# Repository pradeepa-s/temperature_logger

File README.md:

# Temperature Logger

A temperature logger project to start learning fundamentals of product design.

# Tests

## Behavioral

Behavioural tests are implemented for the design and they can be found in tests/behavior folder.

### Setup

1. Install Python 3.6 or above
1. Install behave
1. Install ST-LINK-CLI (comes with STLink utility)
1. Ensure that the ST-LINK-CLI is in the path

### How to run tests?

Run all the tests:

```
behave
```

Run a test with tag @test_tag:

```
behave -t @test_tag
```

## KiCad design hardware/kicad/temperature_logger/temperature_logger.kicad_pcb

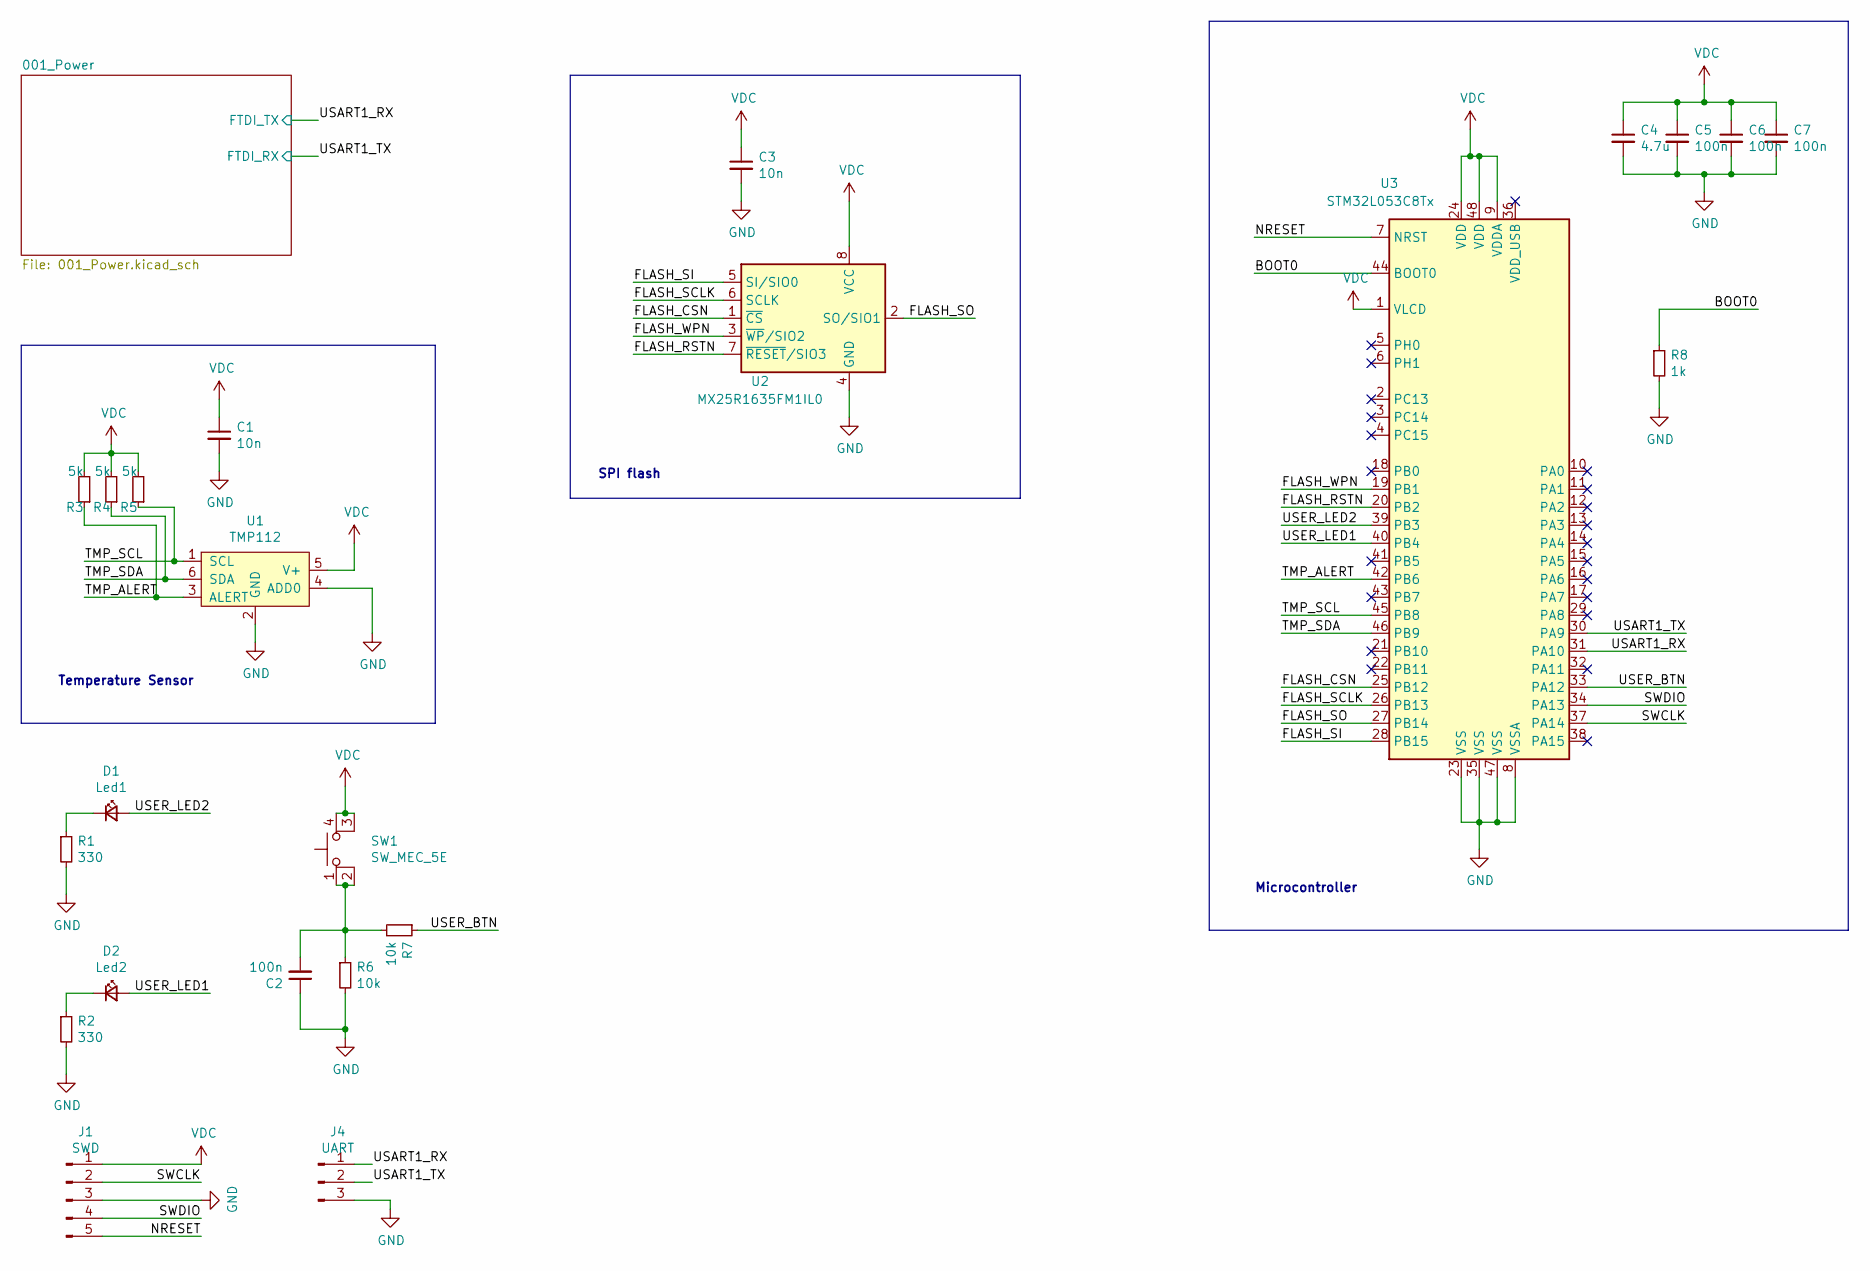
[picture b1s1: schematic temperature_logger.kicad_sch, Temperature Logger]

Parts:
C1, C3: 10n; C_0603_1608Metric_Pad1.08x0.95mm_HandSolder
C2, C5, C6, C7: 100n; C_0603_1608Metric_Pad1.08x0.95mm_HandSolder
C4: 4.7u; C_0603_1608Metric_Pad1.08x0.95mm_HandSolder
D1: Led1; LED_0603_1608Metric_Pad1.05x0.95mm_HandSolder
D2: Led2; LED_0603_1608Metric_Pad1.05x0.95mm_HandSolder
J1: SWD; PinHeader_1x05_P2.54mm_Vertical
J4: UART; PinHeader_1x03_P2.54mm_Vertical
R1, R2: 330; R_0603_1608Metric_Pad1.05x0.95mm_HandSolder
R3, R4, R5: 5k; R_0603_1608Metric_Pad1.05x0.95mm_HandSolder
R6, R7: 10k; R_0603_1608Metric_Pad1.05x0.95mm_HandSolder
R8: 1k; R_0603_1608Metric_Pad1.05x0.95mm_HandSolder
SW1: SW_MEC_5E; SW_SPST_Omron_B3FS-101xP
U1: TMP112; SOT-666
U2: MX25R1635FM1IL0; SOP-8_3.9x4.9mm_P1.27mm
U3: STM32L053C8Tx; LQFP-48_7x7mm_P0.5mm

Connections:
/BOOT0: R8.1, U3.44 (BOOT0)
/FLASH_CSN: U2.1 (~CS), U3.25 (PB12)
/FLASH_RSTN: U2.7 (~RESET/SIO3), U3.20 (PB2)
/FLASH_SCLK: U2.6 (SCLK), U3.26 (PB13)
/FLASH_SI: U2.5 (SI/SIO0), U3.28 (PB15)
/FLASH_SO: U2.2 (SO/SIO1), U3.27 (PB14)
/FLASH_WPN: U2.3 (~WP/SIO2), U3.19 (PB1)
/NRESET: J1.5, U3.7 (NRST)
/SWCLK: J1.2, U3.37 (PA14)
/SWDIO: J1.4, U3.34 (PA13)
/TMP_ALERT: R3.1, U1.3 (ALERT), U3.42 (PB6)
/TMP_SCL: R5.1, U1.1 (SCL), U3.45 (PB8)
/TMP_SDA: R4.1, U1.6 (SDA), U3.46 (PB9)
/USART1_RX: J4.1, U3.31 (PA10); also elsewhere on the board
/USART1_TX: J4.2, U3.30 (PA9); also elsewhere on the board
/USER_BTN: R7.1, U3.33 (PA12)
/USER_LED1: D2.2 (A), U3.40 (PB4)
/USER_LED2: D1.2 (A), U3.39 (PB3)
GND: C1.2, C2.1, C3.2, C4.2, C5.2, C6.2, C7.2, J1.3, J4.3, R1.2, R2.2, R6.2, R8.2, U1.2 (GND), U1.4 (ADD0), U2.4 (GND), U3.8 (VSSA), U3.23 (VSS), U3.35 (VSS), U3.47 (VSS); also elsewhere on the board
unnamed: C2.2, R6.1, R7.2, SW1.1, SW1.2
unnamed: D1.1 (K), R1.1
unnamed: D2.1 (K), R2.1
VDC: C1.1, C3.1, C4.1, C5.1, C6.1, C7.1, J1.1, R3.2, R4.2, R5.2, SW1.3 (K), SW1.4 (A), U1.5 (V+), U2.8 (VCC), U3.1 (VLCD), U3.9 (VDDA), U3.24 (VDD), U3.48 (VDD); also elsewhere on the board

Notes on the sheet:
Microcontroller
SPI flash
Temperature Sensor

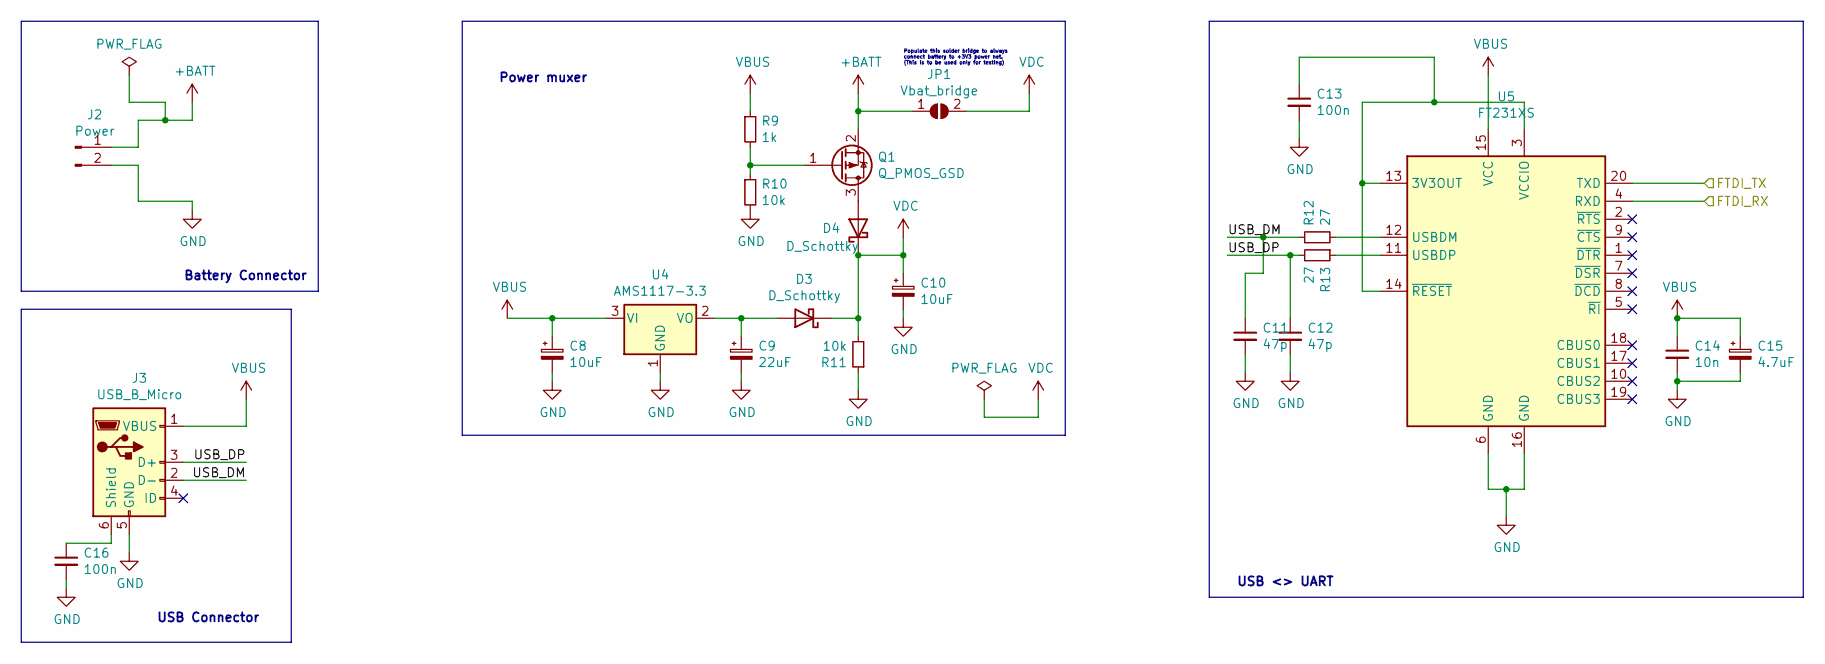
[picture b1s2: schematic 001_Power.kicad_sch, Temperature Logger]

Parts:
C8, C10: 10uF; CP_Elec_4x5.7
C9: 22uF; CP_Elec_4x5.7
C11, C12: 47p; C_0603_1608Metric_Pad1.08x0.95mm_HandSolder
C13, C16: 100n; C_0603_1608Metric_Pad1.08x0.95mm_HandSolder
C14: 10n; C_0603_1608Metric_Pad1.08x0.95mm_HandSolder
C15: 4.7uF; CP_Elec_4x5.7
D3, D4: D_Schottky; D_SOD-323_HandSoldering
J2: Power; BatteryHolder_Keystone_1060_1x2032
J3: USB_B_Micro; USB_Micro-B_Molex-105017-0001
JP1: Vbat_bridge; R_0603_1608Metric
Q1: Q_PMOS_GSD; SOT-23
R9: 1k; R_0603_1608Metric_Pad1.05x0.95mm_HandSolder
R10, R11: 10k; R_0603_1608Metric_Pad1.05x0.95mm_HandSolder
R12, R13: 27; R_0603_1608Metric_Pad1.05x0.95mm_HandSolder
U4: AMS1117-3.3; SOT-223-3_TabPin2
U5: FT231XS; SSOP-20_3.9x8.7mm_P0.635mm

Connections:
+BATT: J2.1, JP1.1 (A), Q1.2 (S)
/001_Power/USB_DM: C11.1, J3.2 (D-), R12.1
/001_Power/USB_DP: C12.1, J3.3 (D+), R13.2
/USART1_RX: U5.20 (TXD); also elsewhere on the board
/USART1_TX: U5.4 (RXD); also elsewhere on the board
GND: C8.2, C9.2, C10.2, C11.2, C12.2, C13.2, C14.2, C15.2, C16.2, J2.2, J3.5 (GND), R10.2, R11.1, U4.1 (GND), U5.6 (GND), U5.16 (GND); also elsewhere on the board
unnamed: C13.1, U5.3 (VCCIO), U5.13 (3V3OUT), U5.14 (~RESET)
unnamed: C16.1, J3.6 (Shield)
unnamed: C9.1, D3.2 (A), U4.2 (VO)
unnamed: D4.2 (A), Q1.3 (D)
unnamed: Q1.1 (G), R9.2, R10.1
unnamed: R12.2, U5.12 (USBDM)
unnamed: R13.1, U5.11 (USBDP)
VBUS: C8.1, C14.1, C15.1, J3.1 (VBUS), R9.1, U4.3 (VI), U5.15 (VCC)
VDC: C10.1, D3.1 (K), D4.1 (K), JP1.2 (B), R11.2; also elsewhere on the board

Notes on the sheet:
Battery Connector
USB Connector
Populate this solder bridge to always connect battery to +3V3 power net. (This is to be used only for testing)
Power muxer
USB <> UART

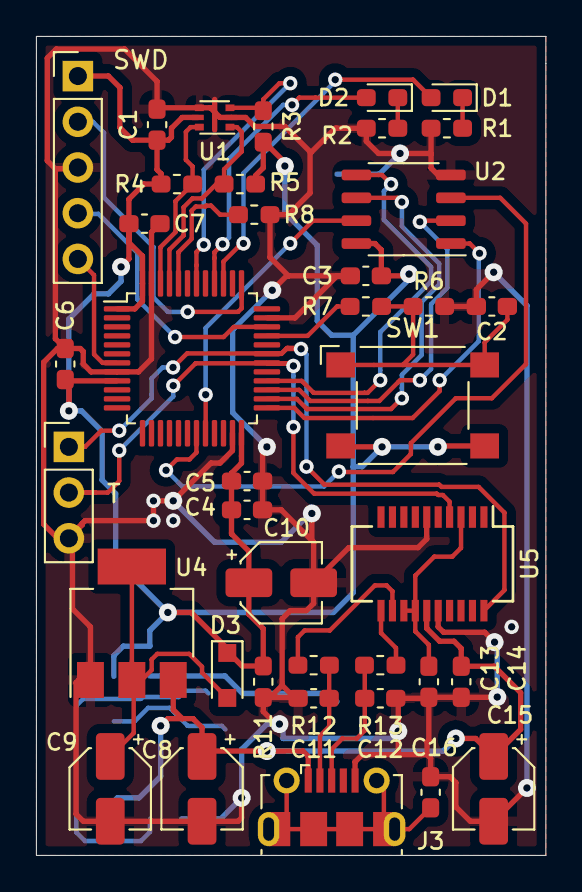
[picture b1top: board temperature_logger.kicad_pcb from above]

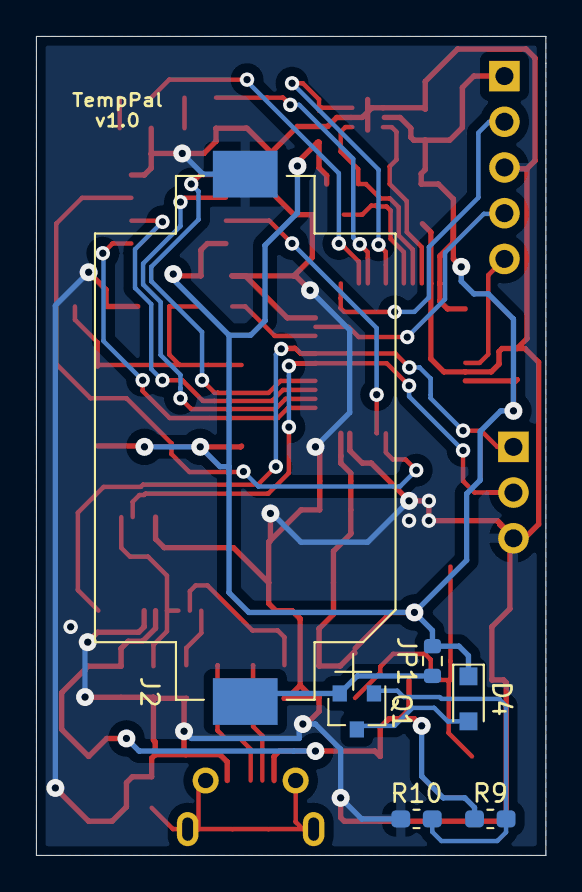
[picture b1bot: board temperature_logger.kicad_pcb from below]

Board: 2 copper layers, 28.3 x 45.5 mm, 45 parts (6 on the bottom side), 34 nets.

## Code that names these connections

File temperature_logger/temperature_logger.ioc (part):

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Mcu.Name=STM32L053C(6-8)Tx
Mcu.Package=LQFP48
Mcu.UserName=STM32L053C8Tx
PA0.GPIOParameters=GPIO_PuPd,GPIO_Label,GPIO_ModeDefaultEXTI
PA0.GPIO_Label=B1 [Blue PushButton]
PA0.GPIO_ModeDefaultEXTI=GPIO_MODE_EVT_RISING
PA0.GPIO_PuPd=GPIO_NOPULL
PA0.Signal=GPXTI0
PA1.GPIOParameters=GPIO_Label
PA1.GPIO_Label=MFX_WAKEUP
PA1.Signal=GPIO_Input
PA10.GPIOParameters=GPIO_Label
PA10.GPIO_Label=USART_RX
PA10.Mode=Asynchronous
PA10.Signal=USART1_RX
PA11.GPIOParameters=GPIO_Label
PA11.GPIO_Label=USB1_DM
PA11.Signal=USB_DM
PA12.GPIOParameters=GPIO_Label
PA12.GPIO_Label=USB1_DP
PA12.Signal=USB_DP
PA13.GPIOParameters=GPIO_Label
PA13.GPIO_Label=SWDIO
PA13.Signal=SYS_SWDIO
PA15.GPIOParameters=GPIO_Speed,GPIO_PuPd,GPIO_Label,GPIO_Mode
PA15.GPIO_Label=ePD1_CS [ePaper_CS\#]
PA15.GPIO_Mode=GPIO_MODE_AF_PP
PA15.GPIO_PuPd=GPIO_NOPULL
PA15.GPIO_Speed=GPIO_SPEED_FREQ_LOW
PA15.Signal=SPI1_NSS
PA2.Signal=TSC_G1_IO3
PA3.Signal=TSC_G1_IO4
PA5.GPIOParameters=GPIO_Speed,GPIO_PuPd,GPIO_Label,GPIO_ModeDefaultOutputPP
PA5.GPIO_Label=LD_R [LD4 Red Led]
PA5.GPIO_ModeDefaultOutputPP=GPIO_MODE_OUTPUT_PP
PA5.GPIO_PuPd=GPIO_NOPULL
PA5.GPIO_Speed=GPIO_SPEED_FREQ_LOW
PA5.Signal=GPIO_Output
PA6.Signal=TSC_G2_IO3
PA7.Signal=TSC_G2_IO4
PA8.GPIOParameters=GPIO_PuPd,GPIO_Label,GPIO_Mode
PA8.GPIO_Label=ePD1_BUSY [ePaper_BUSY]
PA8.GPIO_Mode=GPIO_MODE_INPUT
PA8.GPIO_PuPd=GPIO_NOPULL
PA8.Signal=GPIO_Input
PA9.GPIOParameters=GPIO_Label
PA9.GPIO_Label=USART_TX
PA9.Mode=Asynchronous
PA9.Signal=USART1_TX
PB0.Signal=TSC_G3_IO2
PB1.Signal=TSC_G3_IO3
PB10.GPIOParameters=GPIO_Speed,GPIO_PuPd,GPIO_Label,GPIO_ModeDefaultOutputPP
PB10.GPIO_Label=ePD1_PWR_ENn [ePaper_PowerOn]
PB10.GPIO_ModeDefaultOutputPP=GPIO_MODE_OUTPUT_PP
PB10.GPIO_PuPd=GPIO_NOPULL
PB10.GPIO_Speed=GPIO_SPEED_FREQ_LOW
PB10.Signal=GPIO_Output
PB11.GPIOParameters=GPIO_Speed,GPIO_PuPd,GPIO_Label,GPIO_ModeDefaultOutputPP
PB11.GPIO_Label=ePD1_D/C [ePaper_D/C\#]
PB11.GPIO_ModeDefaultOutputPP=GPIO_MODE_OUTPUT_PP
PB11.GPIO_PuPd=GPIO_NOPULL
PB11.GPIO_Speed=GPIO_SPEED_FREQ_LOW
PB11.Signal=GPIO_Output
PB12.GPIOParameters=GPIO_Label
PB12.GPIO_Label=NFC_NSS
PB12.Signal=SPI2_NSS
PB13.GPIOParameters=GPIO_Label
PB13.GPIO_Label=NFC_SCK
PB13.Signal=SPI2_SCK
PB14.GPIOParameters=GPIO_Label
PB14.GPIO_Label=NFC_MISO
PB14.Signal=SPI2_MISO
PB15.GPIOParameters=GPIO_Label
PB15.GPIO_Label=NFC_MOSI
PB15.Signal=SPI2_MOSI
PB2.GPIOParameters=GPIO_Speed,GPIO_PuPd,GPIO_Label,GPIO_ModeDefaultOutputPP
PB2.GPIO_Label=ePD1_RESET [ePaper_RES\#]
PB2.GPIO_ModeDefaultOutputPP=GPIO_MODE_OUTPUT_PP
PB2.GPIO_PuPd=GPIO_NOPULL
PB2.GPIO_Speed=GPIO_SPEED_FREQ_LOW
PB2.Signal=GPIO_Output
PB3.GPIOParameters=GPIO_Speed,GPIO_PuPd,GPIO_Label,GPIO_Mode
PB3.GPIO_Label=ePD1_SCK [ePaper_SCK]
PB3.GPIO_Mode=GPIO_MODE_AF_PP
PB3.GPIO_PuPd=GPIO_NOPULL
PB3.GPIO_Speed=GPIO_SPEED_FREQ_LOW
PB3.Signal=SPI1_SCK
PB4.GPIOParameters=GPIO_Speed,GPIO_PuPd,GPIO_Label,GPIO_ModeDefaultOutputPP
PB4.GPIO_Label=LD_G [LD3 Green Led]
PB4.GPIO_ModeDefaultOutputPP=GPIO_MODE_OUTPUT_PP
PB4.GPIO_PuPd=GPIO_NOPULL
PB4.GPIO_Speed=GPIO_SPEED_FREQ_LOW
PB4.Signal=GPIO_Output
PB5.GPIOParameters=GPIO_Speed,GPIO_PuPd,GPIO_Label,GPIO_Mode
PB5.GPIO_Label=ePD1_MOSI [ePaper_MOSI]
PB5.GPIO_Mode=GPIO_MODE_AF_PP
PB5.GPIO_PuPd=GPIO_NOPULL
PB5.GPIO_Speed=GPIO_SPEED_FREQ_LOW
PB5.Signal=SPI1_MOSI
PB8.GPIOParameters=GPIO_Label
PB8.GPIO_Label=MFX_I2C_SCL
PB8.Signal=I2C1_SCL
PB9.GPIOParameters=GPIO_Label
PB9.GPIO_Label=MFX_I2C_SDA
PB9.Signal=I2C1_SDA
PC13.GPIOParameters=GPIO_Label
PC13.GPIO_Label=MFX_IRQ_OUT
PC13.Signal=GPXTI13
PC14-OSC32_IN.GPIOParameters=GPIO_Label
PC14-OSC32_IN.GPIO_Label=PC14-OSC32_IN
PC14-OSC32_IN.Signal=RCC_OSC32_IN
PC15-OSC32_OUT.GPIOParameters=GPIO_Label
PC15-OSC32_OUT.GPIO_Label=PC15-OSC32_OUT
PC15-OSC32_OUT.Signal=RCC_OSC32_OUT
PH0-OSC_IN.GPIOParameters=GPIO_Label
PH0-OSC_IN.GPIO_Label=MCO
PH0-OSC_IN.Signal=RCC_OSC_IN
RCC.HSE_VALUE=8000000
RCC.SYSCLKFreq_VALUE=16000000
RCC.SYSCLKSource=RCC_SYSCLKSOURCE_PLLCLK
board=STM32L0538-DISCO
boardIOC=true

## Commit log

2017-11-26 Added GPIO toggle
2017-11-26 Added the error handler to blink red led
2017-11-26 Added UART
2017-11-26 Added printf support
2017-11-26 Added RTC configuration
2017-11-26 Added RTC interrupt to display time and set alarm
2017-11-26 Implemented the scanf function
2020-10-21 Added altium files
2021-06-23 Half way through the PCB
2021-06-26 Main rounting done for pass 2
2021-07-24 Hardware routing completed (verification required)
2021-08-01 TLP1-5: First commit
2021-08-10 Added the test_fw
2021-08-13 Implemented the single button press logic
2021-08-27 Added upto storage
2021-08-28 Added a simple send to PC
2021-08-28 Added read all to PC
2021-08-28 Added firmware architecture
2021-08-28 Added RTC time
2021-08-28 Added logging every 10 seconds
2021-08-28 integrated the temperature sensor
2021-08-29 Updated the command parser and added some python scripts to test
2021-09-04 Added low power mode and refactored the code
2021-09-04 Removed unused projects
2021-09-12 Added schematic changes
2021-10-21 Added behave based tests
2021-10-21 Updated the readme
2021-10-21 Updated the diagrams
2022-12-06 Temperature logging and RTC is working
2022-12-14 Fixed button bug
2022-12-21 TEM-4: Added planning documents for V2
2023-06-29 Removed old firmware implementation
2023-07-01 Extracted footprints and schematics
2023-07-01 TLV-8: Blinking LED
2023-07-01 TLV-8: Minimal debug printf
2023-07-03 TLV-8: Day 3 implementing debug printf
2023-07-11 TLV-8: Implemented debug printf support
2023-07-11 TLV-8: Removed unused functions
2023-07-15 TLV-9: Implemented the temperature sensor basic
2023-07-18 TLV-9: Moved tmp112 to separate files
2023-07-18 TLV-9: Basic temperature logger driver
2023-07-22 TLV-10: Implemented the basic RTC code
2023-07-22 TLV-10: Implement basic RTC code
2023-08-06 TLV-10: Debug printf and transport layer
2023-08-06 TLV-14: Debug printf and transport layer
2023-08-11 Implementing transport layer command rx
2023-08-16 Implemented simple command parser
2023-08-17 Added some #defines
2023-08-18 Added simple response generator
2023-08-19 Fixed a minor issue
2023-08-19 TLV-15: Implement GetStatus command
    * Implement transport layer
    * Implement command parser for get status command
    * Implement response generator for get status command
2023-08-27 TLV-16: Implemented SetDatetime command
2023-08-27 TLV-16: Implemented SetDatetime command (#7)
2024-01-23 TLV-17: Added spi configuration
2024-02-18 TLV-17: Erase storage manager
2024-02-19 TLV-17: Added the chip erase command
2024-02-21 TLV-17: Refactor
2024-02-21 TLV-17: Added docs and defs
2024-02-21 TLV-17: Chip erase command and functionality
